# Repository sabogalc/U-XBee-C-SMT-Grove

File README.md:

# U-XBee-C SMT Grove
This is a reverse-engineered Digi XBee Grove (SMT) with a USB-C connector. I will document how I made this board as well as what you should look out for if you are looking to do something similar.

Thankfully, lots of the documentation around this board is public, and I would not have been able to make this project without the documentation. That being said, some of the documentation is incorrect or mismatched, so I will aim to make some corrections in this write-up.

The first things I referenced were the [schematic and Gerber files](https://www.digi.com/resources/documentation/DigiDocs/90001457-13/reference/r_xbee_grove_development_schematic_smt.htm) directly from Digi, and I was excited at the prospect of being able to take these Gerbers and easily make a board from them. From there, I would just swap the USB port and call it a day, but unfortunately it was not this easy.

When I viewed the Gerbers, I noticed some weird artifacts in the bottom left corner that you can see below. These were present no matter what software I was using to view them.

On taking a closer look, I found what were some very usable Gerbers, but unfortunately I was not successful in reversing them to make a board in either KiCad or Altium Designer. I referenced [this guide](https://www.altium.com/documentation/knowledge-base/altium-designer/convert-gerber-odb-fabrication-data-back-to-pcb) for Altium and [this guide](https://forum.kicad.info/t/reverse-engineering-kicad-project-from-gerber-files/30903) for KiCad.

After putting in some effort to get a board file from the Gerbers, I realized that I'd be better off making my own board from scratch while using the Gerbers as a reference. So I got to work on recreating the schematic and footprints.

The most difficulat part of this process was creating the footprint of the board shape and the SMT header pins around the rectangular hole at the top. I spent a long time figuring out what part these headers were as well as what footprint I should use for them. I found [this knowledge base post from Digi](https://www.digi.com/support/knowledge-base/what-type-of-header-is-used-on-the-xbib-u-ss-inter) that revealed the header pins to be a custom part with part number 76002056. This part number shows up in both DigiKey and Mouser, but the product is obsolete. However, even if it wasn't [this StackExchange answer](https://electronics.stackexchange.com/a/195601) indicates that the part cost $40 when it was available "Probably because some poor bastard at Digi whose official position is 'proprietary connector fabricator and needle nose plier operations chief' manufactures them on demand. By hand." That answer gave me a good laugh, but it's probably true.

Digi has a datasheeet for this part with the measurements [here](https://ftp1.digi.com/support/images/3405-SM-socket_hole-placement.pdf), but I personally would not trust the measurements from this document. I won't even go through the effort of correcting everything wrong with it, but the most immediate problem I found was that this document states that the rectangular hole measures 12.065mm x 17.145mm, while the Gerbers indicated that this hole was 14mm x 20mm. I recreated my footprint by following the Gerbers, and if you need a footprint for this part, just use mine. I combined the footprint for the board and the headers into one footprint called "XBEE_SMT" in the footprints library of this project.

>XBEE_SMT footprint from this project complete with the board shape, header pin holes, and fiducial markers.

The documentation for the board shape was a little better, but it still had a few issues. You can find the mechanical specifications [here](https://www.digi.com/resources/documentation/digidocs/pdfs/90001457-13.pdf#page=12), but they are incorrect by a factor of 0.04mm at the top. The corrected measurements are below. The documentation does not give measurements for the Non-Plated Through Holes in each corner of the board, but I got those from the Gerber files (the top two are 3.24mm in diameter and the bottom two are 3.2mm in diameter).

At this point, the hardest part was done, and I got to recreating the schematic. I was able to find [a bill of materials](https://media.digikey.com/pdf/Reference%20Design/Digi%20International%20Ref%20Designs/XBee_Grove_Dev_Brd_BOM.pdf) for this board (or for the THT version, I couldn't really tell), and this was very useful in obtaining footprints for parts such as the common mode choke or the potentiometer.

Notably, the BOM refers to the 4-pin Grove headers as ACC391450, but I could not find anything for this part number. 110990030 appears to be the exact same part, and this is the one I used for my project. Another discrepancy with the BOM is that it states the 10uF capacitors are size 0402/1005 Metric, but they appear to be 0603/1608 Metric at least, so I manually edited that. Additionally, the LTST-C190CKT red LED is obsolete, so I swapped it with a QBLP601-R5 LED if you were to actually make this with new parts and not just take them from an XBee Grove. Lastly, the part number given for the LED labeled "Green" in the schematic is a blue one, but this should not be a big deal.

With all of the parts imported and the schematic recreated (PDF version [here](https://github.com/sabogalc/U-XBee-C-SMT-Grove/blob/main/XBEE%20Grove%20C/XBEE%20Grove%20C.pdf)), the last thing to do was to route everything on the board. Once again, I did my best to reference the Gerber files and match the placement of the components, tracks, vias, and silkscreen. Once it was all said and done, I found my board to be quite similar to the original.

All in all, I am happy with how this project turned out, and if further improvements to the board could be made, I would be happy to implement them. Thanks for reading!

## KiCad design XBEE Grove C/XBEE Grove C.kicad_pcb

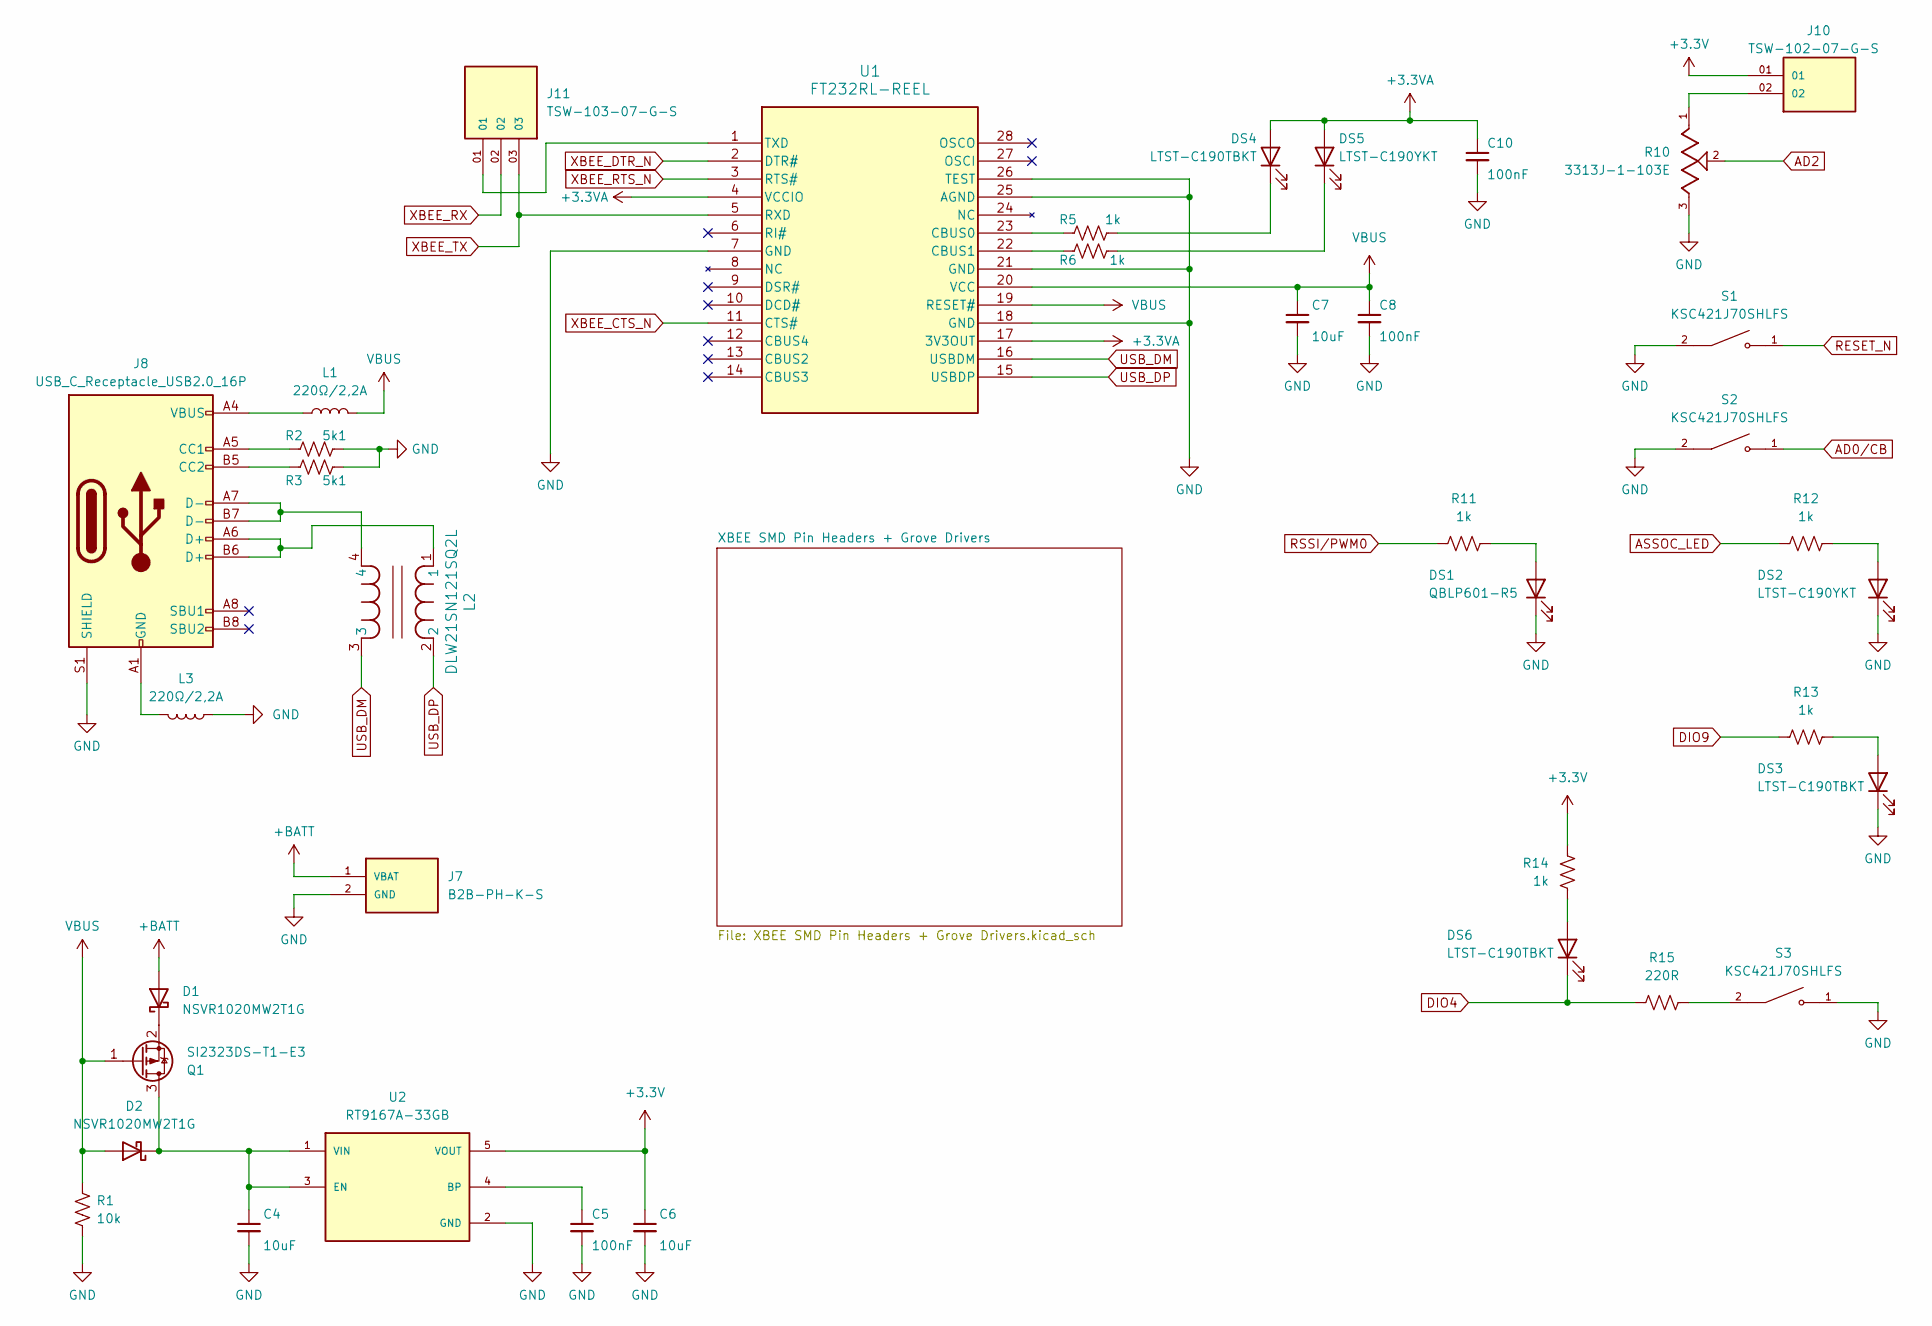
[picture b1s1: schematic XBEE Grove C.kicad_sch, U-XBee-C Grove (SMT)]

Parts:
C4, C6, C7: 10uF; C_0603_1608Metric
C5, C8, C10: 100nF; C_0402_1005Metric
D1, D2: NSVR1020MW2T1G; D_SOD-323
DS1: QBLP601-R5; LED_0603_1608Metric
DS2, DS5: LTST-C190YKT; LED_0603_1608Metric
DS3, DS4, DS6: LTST-C190TBKT; LED_0603_1608Metric
J7: B2B-PH-K-S; JST_B2B-PH-K-S
J8: USB_C_Receptacle_USB2.0_16P; USB_C_Receptacle_GCT_USB4105-xx-A_16P_TopMnt_Horizontal
J10: TSW-102-07-G-S; SAMTEC_TSW-102-07-G-S
J11: TSW-103-07-G-S; SAMTEC_TSW-103-07-G-S
L1, L3: 220Ω/2,2A; L_0603_1608Metric
L2: DLW21SN121SQ2L; IND_DLW21S_0805_MUR
Q1: SI2323DS-T1-E3; SOT-23
R1: 10k; R_0402_1005Metric
R2, R3: 5k1; R_0402_1005Metric
R5, R6, R11, R12, R13, R14: 1k; R_0402_1005Metric
R10: 3313J-1-103E; TRIM_3313J-1-103E
R15: 220R; R_0402_1005Metric
S1, S2, S3: KSC421J70SHLFS; SW_KSC421J70SHLFS
U1: FT232RL-REEL; IC28_SSOP-28_FTD
U2: RT9167A-33GB; SOT-23-5

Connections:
+3.3V: C6.1, J10.01, R14.2, U2.5 (VOUT); also elsewhere on the board
+3.3VA: C10.1, DS4.2 (A), DS5.2 (A), U1.4 (VCCIO), U1.17 (3V3OUT)
+BATT: D1.2 (A), J7.1 (VBAT)
AD0/CB: S2.1, S2.4; also elsewhere on the board
AD2: R10.2; also elsewhere on the board
ASSOC_LED: R12.1; also elsewhere on the board
DIO4: DS6.1 (K), R15.1; also elsewhere on the board
DIO9: R13.1; also elsewhere on the board
GND: C4.2, C5.2, C6.2, C7.2, C8.2, C10.2, DS1.1 (K), DS2.1 (K), DS3.1 (K), J7.2 (GND), J8.S1 (SHIELD), L3.1, R1.2, R2.2, R3.2, R10.3, S1.2, S1.3, S2.2, S2.3, S3.1, S3.4, U1.7 (GND), U1.18 (GND), U1.21 (GND), U1.25 (AGND), U1.26 (TEST), U2.2 (GND); also elsewhere on the board
unnamed: D1.1 (K), Q1.2 (S)
unnamed: C4.1, D2.1 (K), Q1.3 (D), U2.1 (VIN), U2.3 (EN)
unnamed: DS1.2 (A), R11.2
unnamed: DS2.2 (A), R12.2
unnamed: DS3.2 (A), R13.2
unnamed: DS4.1 (K), R5.2
unnamed: DS5.1 (K), R6.2
unnamed: DS6.2 (A), R14.1
unnamed: J8.A5 (CC1), R2.1
unnamed: J8.B5 (CC2), R3.1
unnamed: J8.A6 (D+), J8.B6 (D+), L2.1
unnamed: J8.A7 (D-), J8.B7 (D-), L2.4
unnamed: J8.A1 (GND), J8.A12 (GND), J8.B1 (GND), J8.B12 (GND), L3.2
unnamed: J8.A4 (VBUS), J8.A9 (VBUS), J8.B4 (VBUS), J8.B9 (VBUS), L1.1
unnamed: J10.02, R10.1
unnamed: R15.2, S3.2, S3.3
unnamed: R5.1, U1.23 (CBUS0)
unnamed: R6.1, U1.22 (CBUS1)
unnamed: J11.01, U1.1 (TXD)
unnamed: C5.1, U2.4 (BP)
RESET_N: S1.1, S1.4; also elsewhere on the board
RSSI/PWM0: R11.1; also elsewhere on the board
USB_DM: L2.3, U1.16 (USBDM)
USB_DP: L2.2, U1.15 (USBDP)
VBUS: C7.1, C8.1, D2.2 (A), L1.2, Q1.1 (G), R1.1, U1.19 (RESET#), U1.20 (VCC)
XBEE_CTS_N: U1.11 (CTS#); also elsewhere on the board
XBEE_DTR_N: U1.2 (DTR#); also elsewhere on the board
XBEE_RTS_N: U1.3 (RTS#); also elsewhere on the board
XBEE_RX: J11.02; also elsewhere on the board
XBEE_TX: J11.03, U1.5 (RXD); also elsewhere on the board

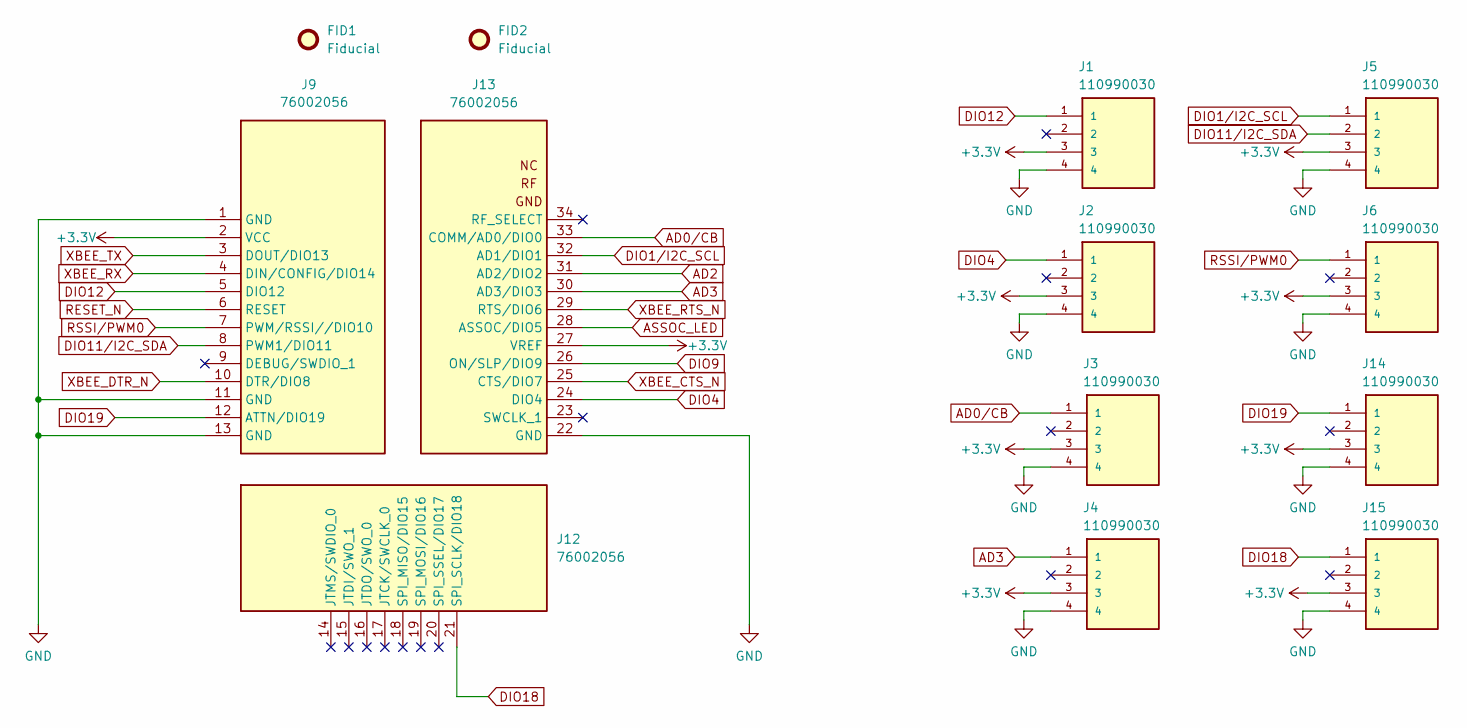
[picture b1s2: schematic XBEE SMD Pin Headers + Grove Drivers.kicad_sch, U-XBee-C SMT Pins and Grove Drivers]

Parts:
FID1, FID2: Fiducial; Fiducial_1mm_Mask2mm
J1, J2, J3, J4, J5, J6, J14, J15: 110990030; SEEED_110990030
J9: 76002056; XBEE_SMT_P1-13
J12: 76002056; XBEE_SMT_P14-21
J13: 76002056; XBEE_SMT_P22-34

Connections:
+3.3V: J1.3, J2.3, J3.3, J4.3, J5.3, J6.3, J9.2 (VCC), J13.27 (VREF), J14.3, J15.3; also elsewhere on the board
AD0/CB: J3.1, J13.33 (COMM/AD0/DIO0); also elsewhere on the board
AD2: J13.31 (AD2/DIO2); also elsewhere on the board
AD3: J4.1, J13.30 (AD3/DIO3)
ASSOC_LED: J13.28 (ASSOC/DIO5); also elsewhere on the board
DIO1/I2C_SCL: J5.1, J13.32 (AD1/DIO1)
DIO4: J2.1, J13.24 (DIO4); also elsewhere on the board
DIO9: J13.26 (ON/SLP/DIO9); also elsewhere on the board
DIO11/I2C_SDA: J5.2, J9.8 (PWM1/DIO11)
DIO12: J1.1, J9.5 (DIO12)
DIO18: J12.21 (SPI_SCLK/DIO18), J15.1
DIO19: J9.12 (ATTN/DIO19), J14.1
GND: J1.4, J2.4, J3.4, J4.4, J5.4, J6.4, J9.1 (GND), J9.11 (GND), J9.13 (GND), J13.22 (GND), J14.4, J15.4; also elsewhere on the board
RESET_N: J9.6 (RESET); also elsewhere on the board
RSSI/PWM0: J6.1, J9.7 (PWM/RSSI//DIO10); also elsewhere on the board
XBEE_CTS_N: J13.25 (CTS/DIO7); also elsewhere on the board
XBEE_DTR_N: J9.10 (DTR/DIO8); also elsewhere on the board
XBEE_RTS_N: J13.29 (RTS/DIO6); also elsewhere on the board
XBEE_RX: J9.4 (DIN/CONFIG/DIO14); also elsewhere on the board
XBEE_TX: J9.3 (DOUT/DIO13); also elsewhere on the board

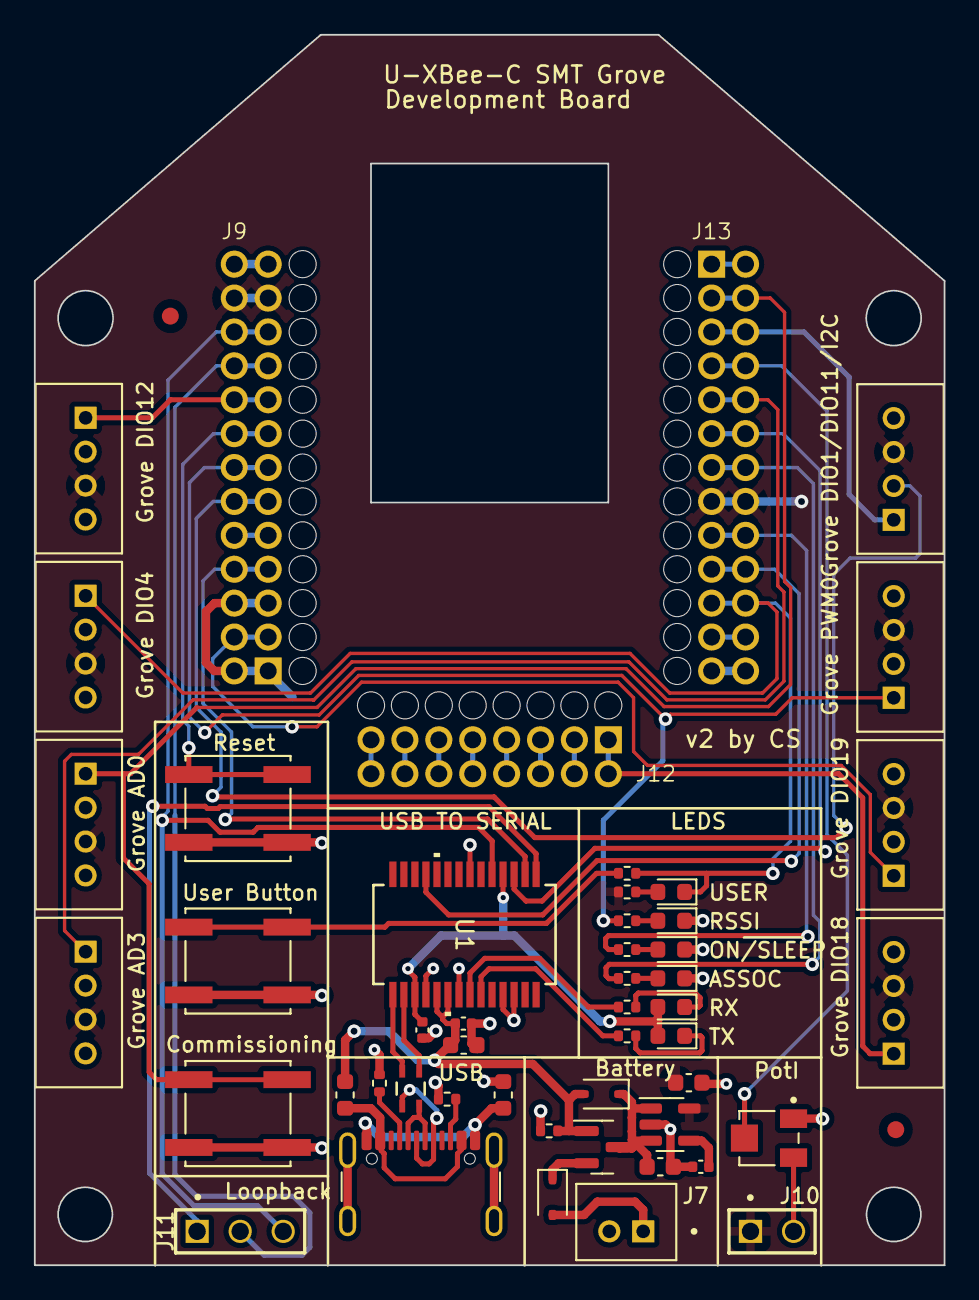
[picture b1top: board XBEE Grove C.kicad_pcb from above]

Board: 2 copper layers, 53.7 x 72.6 mm, 51 parts (0 on the bottom side), 45 nets.

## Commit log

2024-02-05 Delete XBEE Grove C directory
    Deleting old version that used 440054-4 headers instead of 110990030 ones.
2024-02-05 Add files via upload
    Updated board to use the correct 110990030 headers instead of the 440054-4 ones.
2024-02-05 Update README.md
    Fixed typo and updated PDF link.
2024-02-05 Delete XBEE Grove C directory
    Purging to post updated schematic version.
2024-02-05 Add files via upload
    Updated schematic.
2024-02-09 Add files via upload
    Made a slight adjustment to the routing on CC1 and Pad A4/B9.
2024-02-27 Add files via upload
    Corrected L1 and L2 footprints and uploaded boardview file for use with OpenBoardView.
2024-02-28 Add files via upload
    Updated to v2 (all connectors now have the same number scheme as the original).
2024-03-09 Add files via upload
    Updated schematic and boardview to match the original part numbers as best I could.
2024-03-12 Add files via upload
    Uploaded Boardview file with OpenBoardData file.
2024-03-12 Add files via upload
    Included 76002056 part number in the Boardview.
2024-03-12 Add files via upload
    Included 76002056 part number for the SMT connectors.
2024-03-12 Update README.md
    Updated PDF link to be internal.
2024-04-01 Updated boardview file outline
    Used a simplified board outline for the boardview file.
